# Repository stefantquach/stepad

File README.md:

# stepad

# Case notes:
Different material thicknesses (in stack order)
* plate thickness: White Delrin 0.06in (1.524mm)
* open1: White Acrylic 0.12in (3.05mm)
* open2: White Acrylic 0.18in (4.57mm)
* open3: White Acrylic 0.12in (3.05mm)
* bottom: White Acrylic 0.12in (3.05mm). This could be variable thickness and material.

# Build notes:
* Diode direction is reversed.

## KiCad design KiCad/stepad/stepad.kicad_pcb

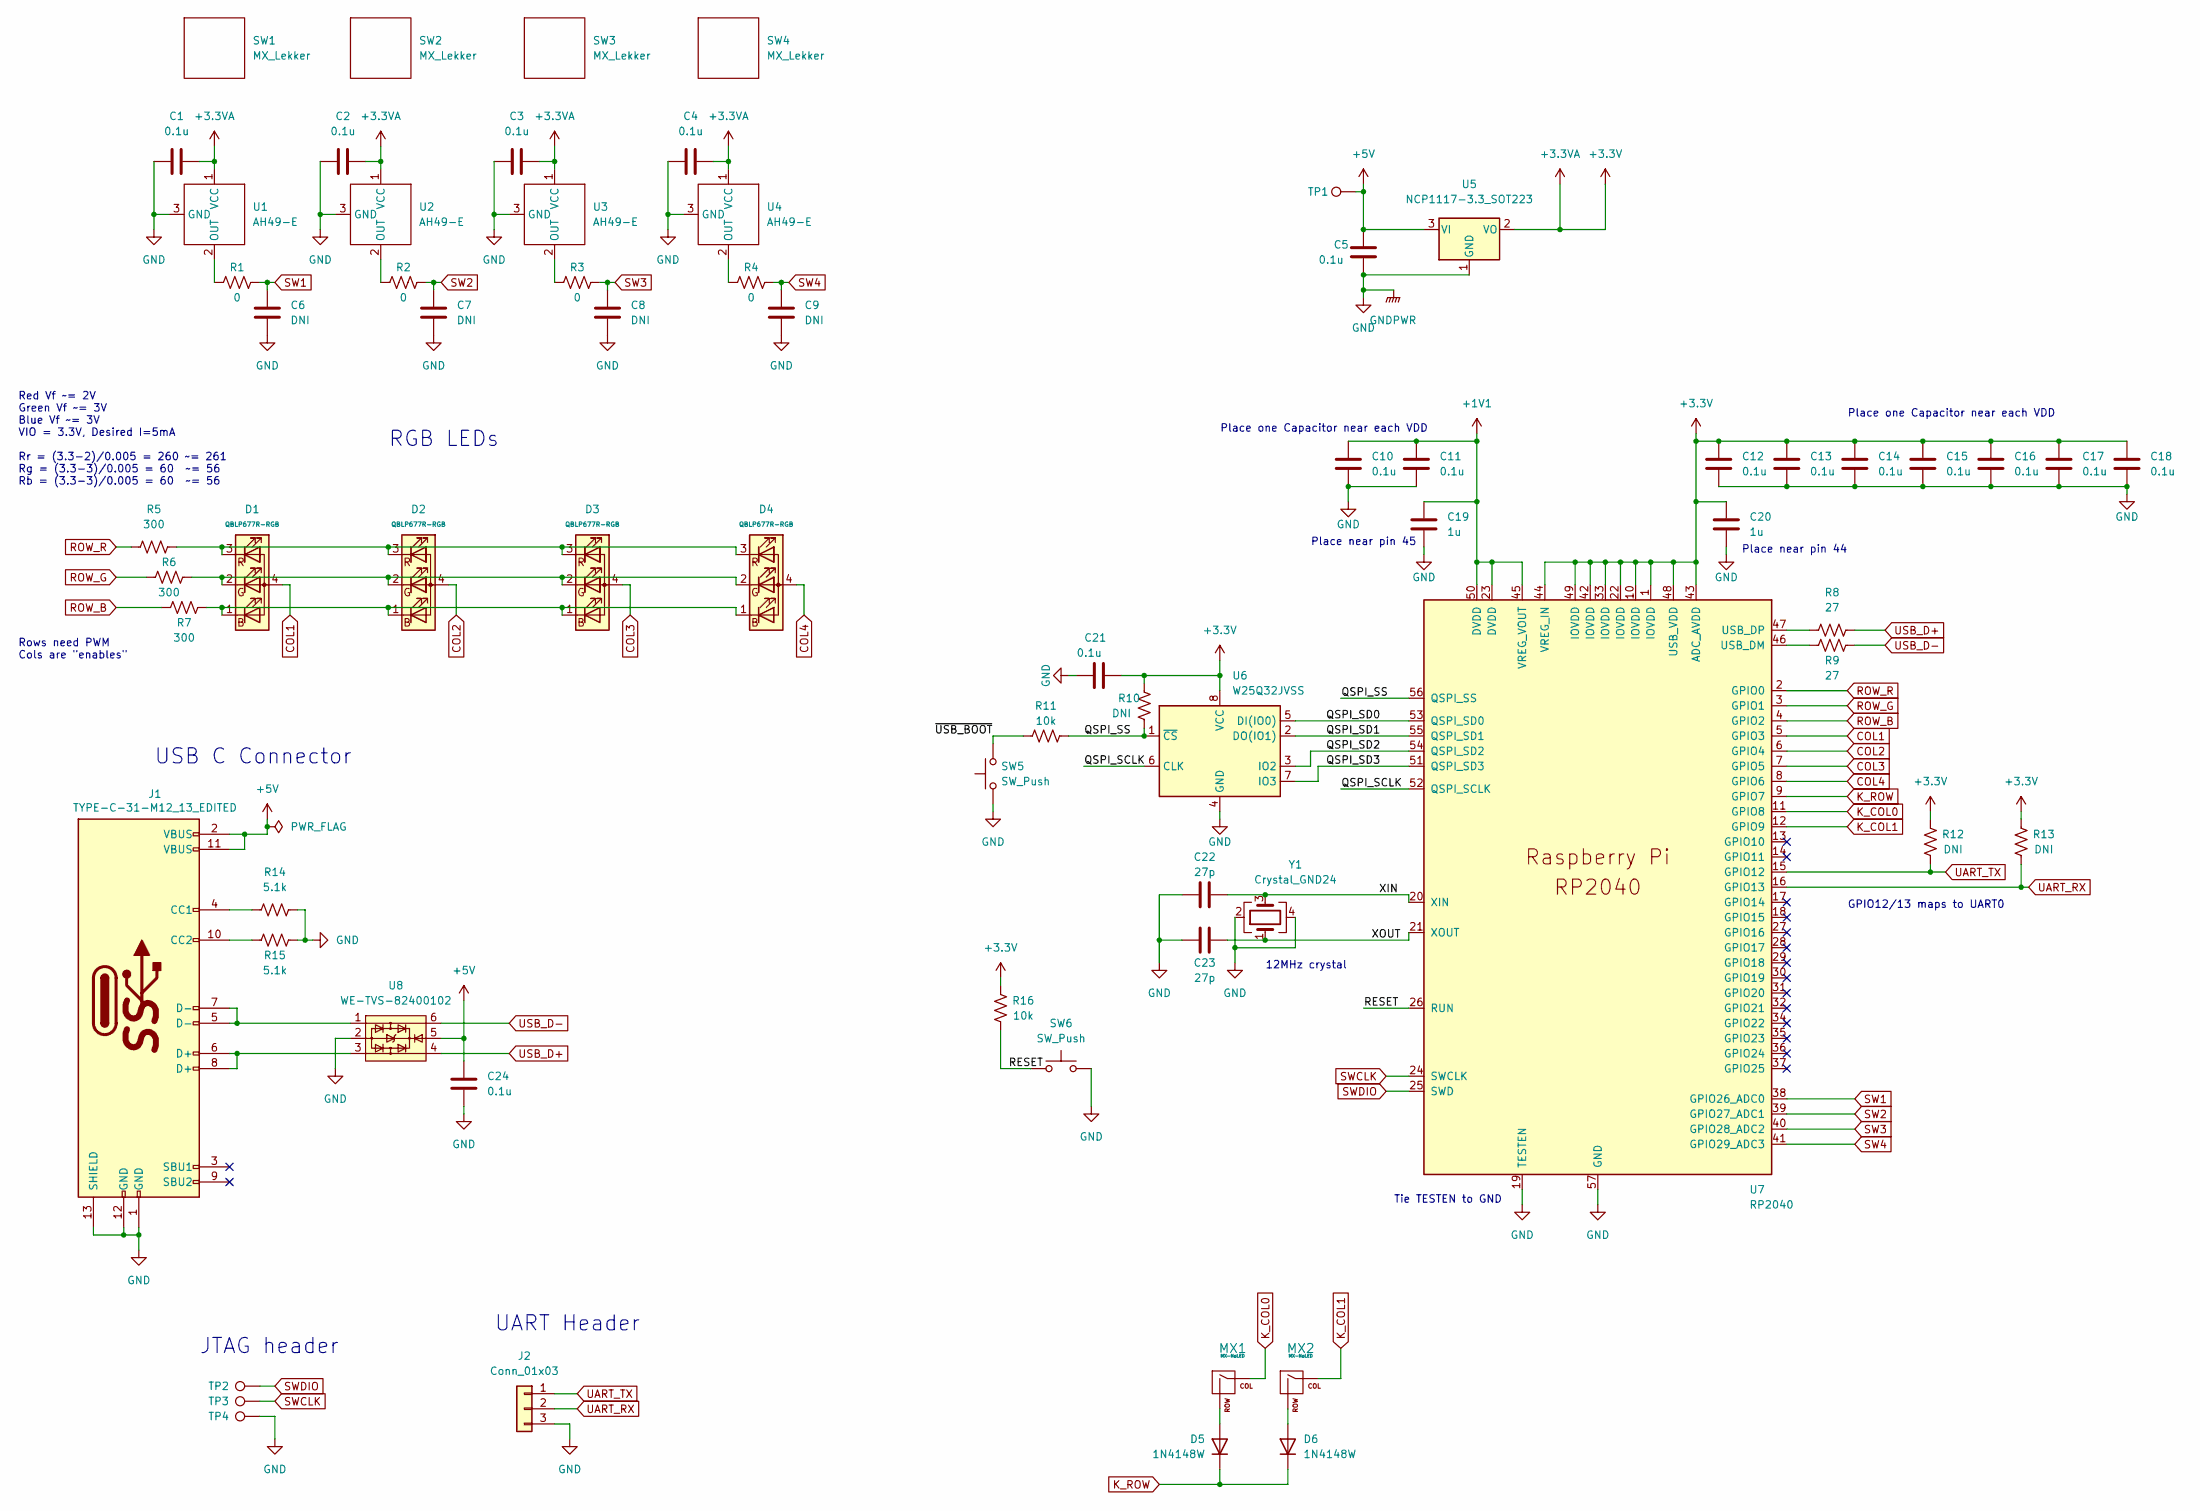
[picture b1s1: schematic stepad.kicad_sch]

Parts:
C1, C2, C3, C4, C5, C10, C11, C12, C13, C14, C15, C16, C17, C18, C21, C24: 0.1u; C_0603_1608Metric_Pad1.08x0.95mm_HandSolder; Part Number C0603C104M4RAC7411
C6, C7, C8, C9: DNI; C_0603_1608Metric_Pad1.08x0.95mm_HandSolder
C19, C20: 1u; C_0603_1608Metric_Pad1.08x0.95mm_HandSolder; Part Number CL10B104KA8NNNC
C22, C23: 27p; C_0603_1608Metric_Pad1.08x0.95mm_HandSolder; Part Number C0603C270J3GAC7867
D1, D2, D3, D4: QBLP677R-RGB; QBLP677R-RGB-square_cutout; Part Number QBLP677R-RGB
D5, D6: 1N4148W; D_SOD-123; Part Number 1N4148W-13-F
J1: TYPE-C-31-M12_13_EDITED; HRO-TYPE-C-31-M-12-HandSoldering; Part Number USB4105-GF-A
J2: Conn_01x03; PinHeader_1x03_P2.54mm_Vertical
MX1, MX2: MX-NoLED; MX-Hotswap-1U
R1, R2, R3, R4: 0; R_0603_1608Metric_Pad0.98x0.95mm_HandSolder; Part Number RC0603FR-070RL
R5, R6, R7: 300; R_0603_1608Metric_Pad0.98x0.95mm_HandSolder; Part Number RC0603JR-07300RL
R8, R9: 27; R_0603_1608Metric_Pad0.98x0.95mm_HandSolder; Part Number RC0603FR-1327RL
R10, R12, R13: DNI; R_0603_1608Metric_Pad0.98x0.95mm_HandSolder
R11, R16: 10k; R_0603_1608Metric_Pad0.98x0.95mm_HandSolder; Part Number RNCP0603FTD10K0
R14, R15: 5.1k; R_0603_1608Metric_Pad0.98x0.95mm_HandSolder; Part Number RC0603FR-135K1L
SW1, SW2, SW3, SW4: MX_Lekker
SW5, SW6: SW_Push; SKQG-1155865; Part Number MSLPT5252AG3TR
TP1, TP2, TP3, TP4: TestPoint; TestPoint_Pad_1.5x1.5mm
U1, U2, U3, U4: AH49-E; SOT-23_Handsoldering_no_plane; Part Number AH49ENTR-G1
U5: NCP1117-3.3_SOT223; SOT-223-3_TabPin2; Part Number AZ1117IH-3.3TRG1
U6: W25Q32JVSS; SOIC-8_5.23x5.23mm_P1.27mm; Part Number W25Q32JVSS
U7: RP2040; RP2040-QFN-56; Part Number SC0914(13)
U8: WE-TVS-82400102; SOT-23-6; Part Number 82400102
Y1: Crystal_GND24; Crystal_SMD_3225-4Pin_3.2x2.5mm; Part Number RH100-12.000-18-2030-TR

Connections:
+1V1: C10.1, C11.1, C19.1, U7.23 (DVDD), U7.45 (VREG_VOUT), U7.50 (DVDD)
+3.3VA: C1.1, C2.1, C3.1, C4.1, C12.1, C13.1, C14.1, C15.1, C16.1, C17.1, C18.1, C20.1, C21.2, R10.2, R12.1, R13.1, R16.1, U1.1 (VCC), U2.1 (VCC), U3.1 (VCC), U4.1 (VCC), U5.2 (VO), U6.8 (VCC), U7.1 (IOVDD), U7.10 (IOVDD), U7.22 (IOVDD), U7.33 (IOVDD), U7.42 (IOVDD), U7.43 (ADC_AVDD), U7.44 (VREG_IN), U7.48 (USB_VDD), U7.49 (IOVDD)
+5V: C5.2, C24.1, J1.2 (VBUS), J1.11 (VBUS), TP1.1, U5.3 (VI), U8.5
/QSPI_SCLK: U6.6 (CLK), U7.52 (QSPI_SCLK)
/QSPI_SD0: U6.5 (DI(IO0)), U7.53 (QSPI_SD0)
/QSPI_SD1: U6.2 (DO(IO1)), U7.55 (QSPI_SD1)
/QSPI_SD2: U6.3 (IO2), U7.54 (QSPI_SD2)
/QSPI_SD3: U6.7 (IO3), U7.51 (QSPI_SD3)
/QSPI_SS: R10.1, R11.2, U6.1 (~CS), U7.56 (QSPI_SS)
/RESET: R16.2, SW6.1, SW6.3, U7.26 (RUN)
/XIN: C22.2, U7.20 (XIN), Y1.3
/XOUT: C23.2, U7.21 (XOUT), Y1.1
/~USB_BOOT: R11.1, SW5.2
COL1: D1.4 (A), U7.5 (GPIO3)
COL2: D2.4 (A), U7.6 (GPIO4)
COL3: D3.4 (A), U7.7 (GPIO5)
COL4: D4.4 (A), U7.8 (GPIO6)
GND: C1.2, C2.2, C3.2, C4.2, C5.1, C6.2, C7.2, C8.2, C9.2, C10.2, C11.2, C12.2, C13.2, C14.2, C15.2, C16.2, C17.2, C18.2, C19.2, C20.2, C21.1, C22.1, C23.1, C24.2, J1.1 (GND), J1.12 (GND), J1.13 (SHIELD), J2.3, R14.2, R15.1, SW5.1, SW6.2, SW6.4, TP4.1, U1.3 (GND), U2.3 (GND), U3.3 (GND), U4.3 (GND), U5.1 (GND), U6.4 (GND), U7.19 (TESTEN), U7.57 (GND), U8.2, Y1.2, Y1.4
K_COL0: MX1.1 (COL), U7.11 (GPIO8)
K_COL1: MX2.1 (COL), U7.12 (GPIO9)
K_ROW: D5.1 (K), D6.1 (K), U7.9 (GPIO7)
unnamed: D1.1 (BK), D2.1 (BK), D3.1 (BK), D4.1 (BK), R7.1
unnamed: D1.2 (GK), D2.2 (GK), D3.2 (GK), D4.2 (GK), R6.2
unnamed: D1.3 (RK), D2.3 (RK), D3.3 (RK), D4.3 (RK), R5.2
unnamed: D5.2 (A), MX1.2 (ROW)
unnamed: D6.2 (A), MX2.2 (ROW)
unnamed: J1.4 (CC1), R14.1
unnamed: J1.5 (D-), J1.7 (D-), U8.1
unnamed: J1.6 (D+), J1.8 (D+), U8.3
unnamed: J1.10 (CC2), R15.2
unnamed: R1.1, U1.2 (OUT)
unnamed: R2.1, U2.2 (OUT)
unnamed: R3.1, U3.2 (OUT)
unnamed: R4.1, U4.2 (OUT)
unnamed: R8.1, U7.47 (USB_DP)
unnamed: R9.2, U7.46 (USB_DM)
ROW_B: R7.2, U7.4 (GPIO2)
ROW_G: R6.1, U7.3 (GPIO1)
ROW_R: R5.1, U7.2 (GPIO0)
SW1: C6.1, R1.2, U7.38 (GPIO26_ADC0)
SW2: C7.1, R2.2, U7.39 (GPIO27_ADC1)
SW3: C8.1, R3.2, U7.40 (GPIO28_ADC2)
SW4: C9.1, R4.2, U7.41 (GPIO29_ADC3)
SWCLK: TP3.1, U7.24 (SWCLK)
SWDIO: TP2.1, U7.25 (SWD)
UART_RX: J2.2, R13.2, U7.16 (GPIO13)
UART_TX: J2.1, R12.2, U7.15 (GPIO12)
USB_D+: R8.2, U8.4
USB_D-: R9.1, U8.6

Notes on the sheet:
Place near pin 44
Rows need PWM Cols are "enables"
USB C Connector
JTAG header
Place one Capacitor near each VDD
RGB LEDs
UART Header
Red Vf ~= 2V Green Vf ~= 3V Blue Vf ~= 3V VIO = 3.3V, Desired I=5mA Rr = (3.3-2)/0.005 = 260 ~= 261 Rg = (3.3-3)/0.005 = 60 ~= 56 Rb = (3.3-3)/0.005 = 60 ~= 56
12MHz crystal
Place near pin 45
Tie TESTEN to GND
GPIO12/13 maps to UART0

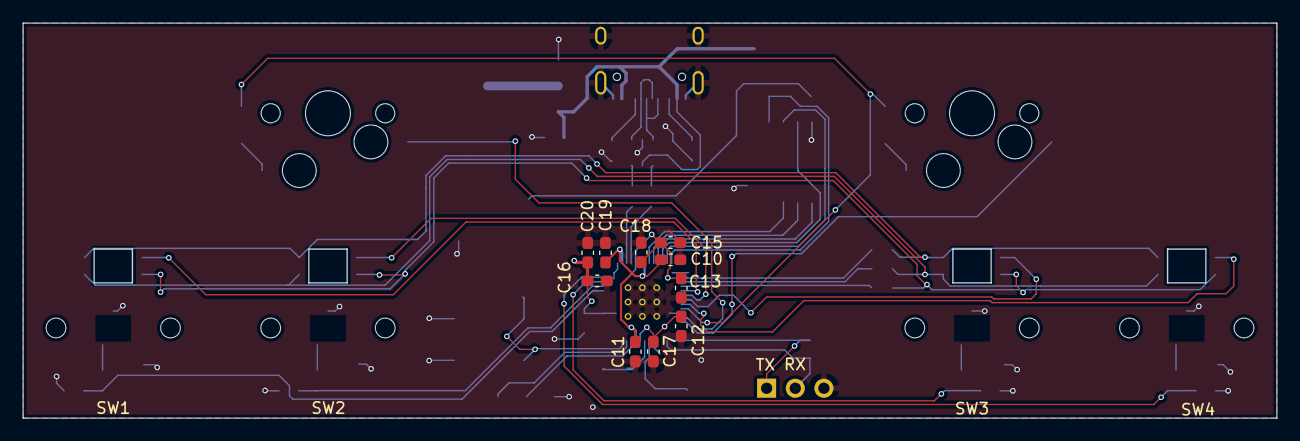
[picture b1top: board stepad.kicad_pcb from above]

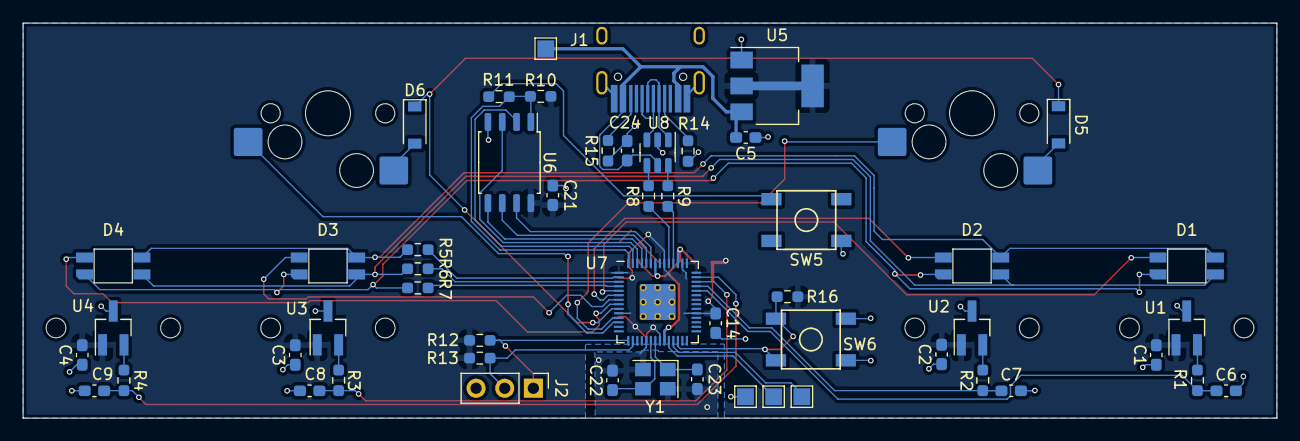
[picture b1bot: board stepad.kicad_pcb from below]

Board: 2 copper layers, 111.2 x 35.0 mm, 69 parts (53 on the bottom side), 49 nets.

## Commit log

2023-05-28 initial design
2023-06-03 Finished initial layout
2023-06-03 Adding part numbers and updating some footprints
2023-06-03 Updating part numbers and gerber files
2023-06-04 Updating gerbers and adding firmware folder
2023-06-10 Adding basic example firmware program
2023-06-22 Remove zephyr stuff. Change to use the RP2040 SDK as a bare metal application
2023-07-17 Adding case DXF files. Firmware WIP, LED matrix now works
2023-07-23 Added firmware for LED matrix and engineering console for calibration procedure
2023-08-10 Added digital switches and basic USB keyboard functionality. WIP keymap, WIP settings, WIP rapid trigger
2023-08-29 WIP hid control interface
2023-09-03 Fixing bugs with hid control interface
2023-09-15 Add rapid trigger implementation
2023-10-01 Implement persistent settings.
2023-10-01 Add rapid trigger sensitivity as a setting.
2023-10-01 Fix bug where rapid trigger mode was not being set properly from HID interface
2023-10-08 Adding version.h header file and add NACK if switch threshold is too small
2023-10-11 Add debug USB console
2023-10-15 Add rapid trigger sensitivity to settings report. Prevent switches running while calibration in progress
2023-10-17 Updating settings scripts
2023-10-28 Add variable length keymap command
